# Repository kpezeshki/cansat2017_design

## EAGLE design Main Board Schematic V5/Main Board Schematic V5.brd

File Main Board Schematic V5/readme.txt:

Readme File for Printed Circuit Board 'GWC Cansat 2017 V4'

Board Specification
Size           89 x 100mm
Material       FR4
No of Layers   3
Thickness      1.6
Finish         HASL (Lead free) (RoHS)
Copper Weight  1.0oz

Special Requirements
Please cut where dimension layer specifies 'CHIP CUTOUT' and the surrounding hashed area.
Please cut where dimension layer specifies 'BOARD CUT' and the hashed area below it. 
Where possible please insert a silkscreen logo using the included file 'tLogo.bmp' in the space provided and named '[LOGO]' on the top silkscreen layer.

The design does not contain Blind Vias		
The design does not contain Buried Vias		
The design does not contain holes smaller than 0.25mm (0.010inches) 

The design conforms to the following design rules

Minimum track thickness 6 mil (0.15mm)
Minimum track clearance 6 mil (0.15mm)  --Not sure, please email 'ccameron12@gwc.org.uk' if there is a problem.

Layer Description
(Note: Inner layers are counted from the top downwards)

Top Silk Screen Overlay		Main Board Schematic V5.GTO
Top Solder Mask			Main Board Schematic V5.GTS
Top Copper			Main Board Schematic V5.GTL
Middle copper			Main Board Schematic V5.LY2
Bottom Copper			Main Board Schematic V5.GBL
Bottom Solder Mask		Main Board Schematic V5.GBS
Bottom Silk Screen		Main Board Schematic V5.GBO
Drill File			Main Board Schematic V5.TXT
Mill Layer			Main Board Schematic V5.GML

Contact Information

Invoice Address
Name           Charles Cameron
Company        GWC Cansat
Address        18 Barnshot Road
City           Edinburgh
County         City of Edinburgh
PostCode       EH13 0DJ
Email          kpezeshki11@gwc.org.uk
Phone          07759796855

Delivery Address
Name           Charles Cameron
Company        GWC Cansat
Address        18 Barnshot Road
City           Edinburgh
County         City of Edinburgh
PostCode       EH13 0DJ
Email          kpezeshki11@gwc.org.uk
Phone          07759796855

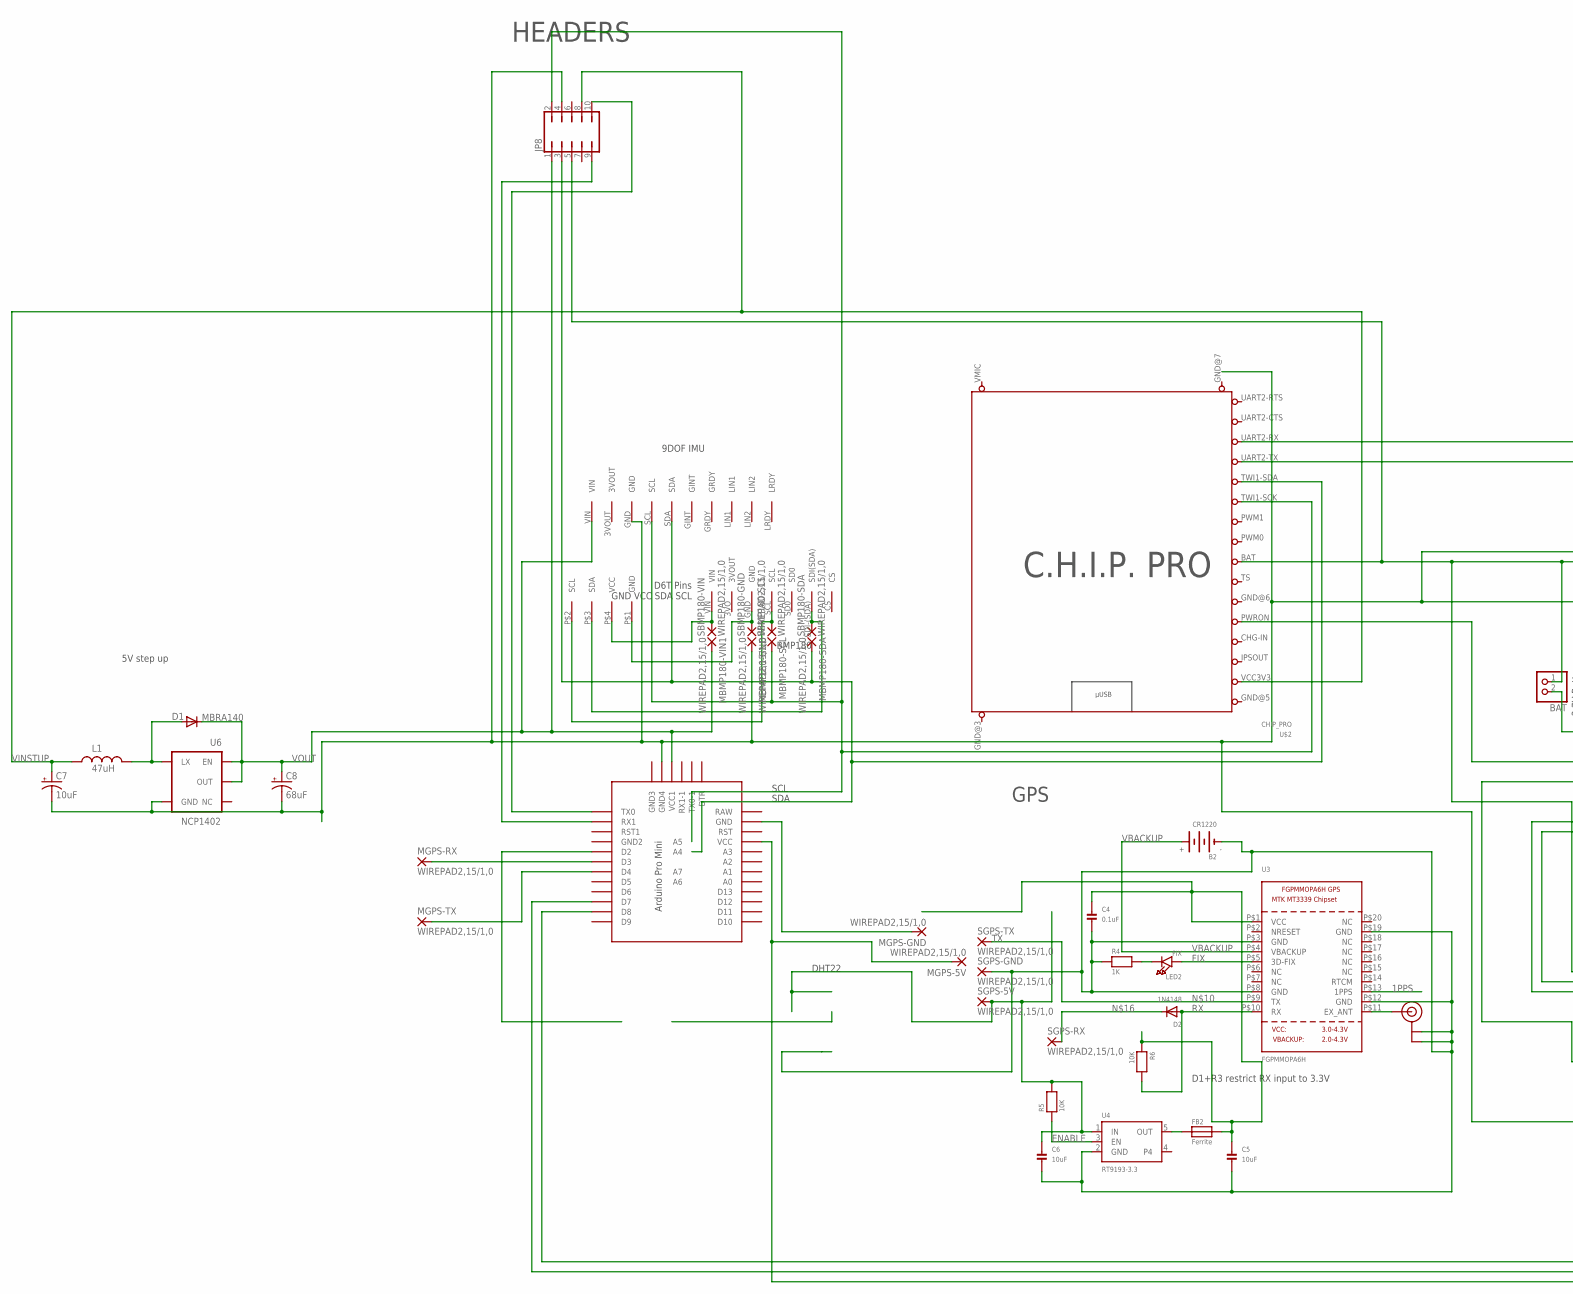
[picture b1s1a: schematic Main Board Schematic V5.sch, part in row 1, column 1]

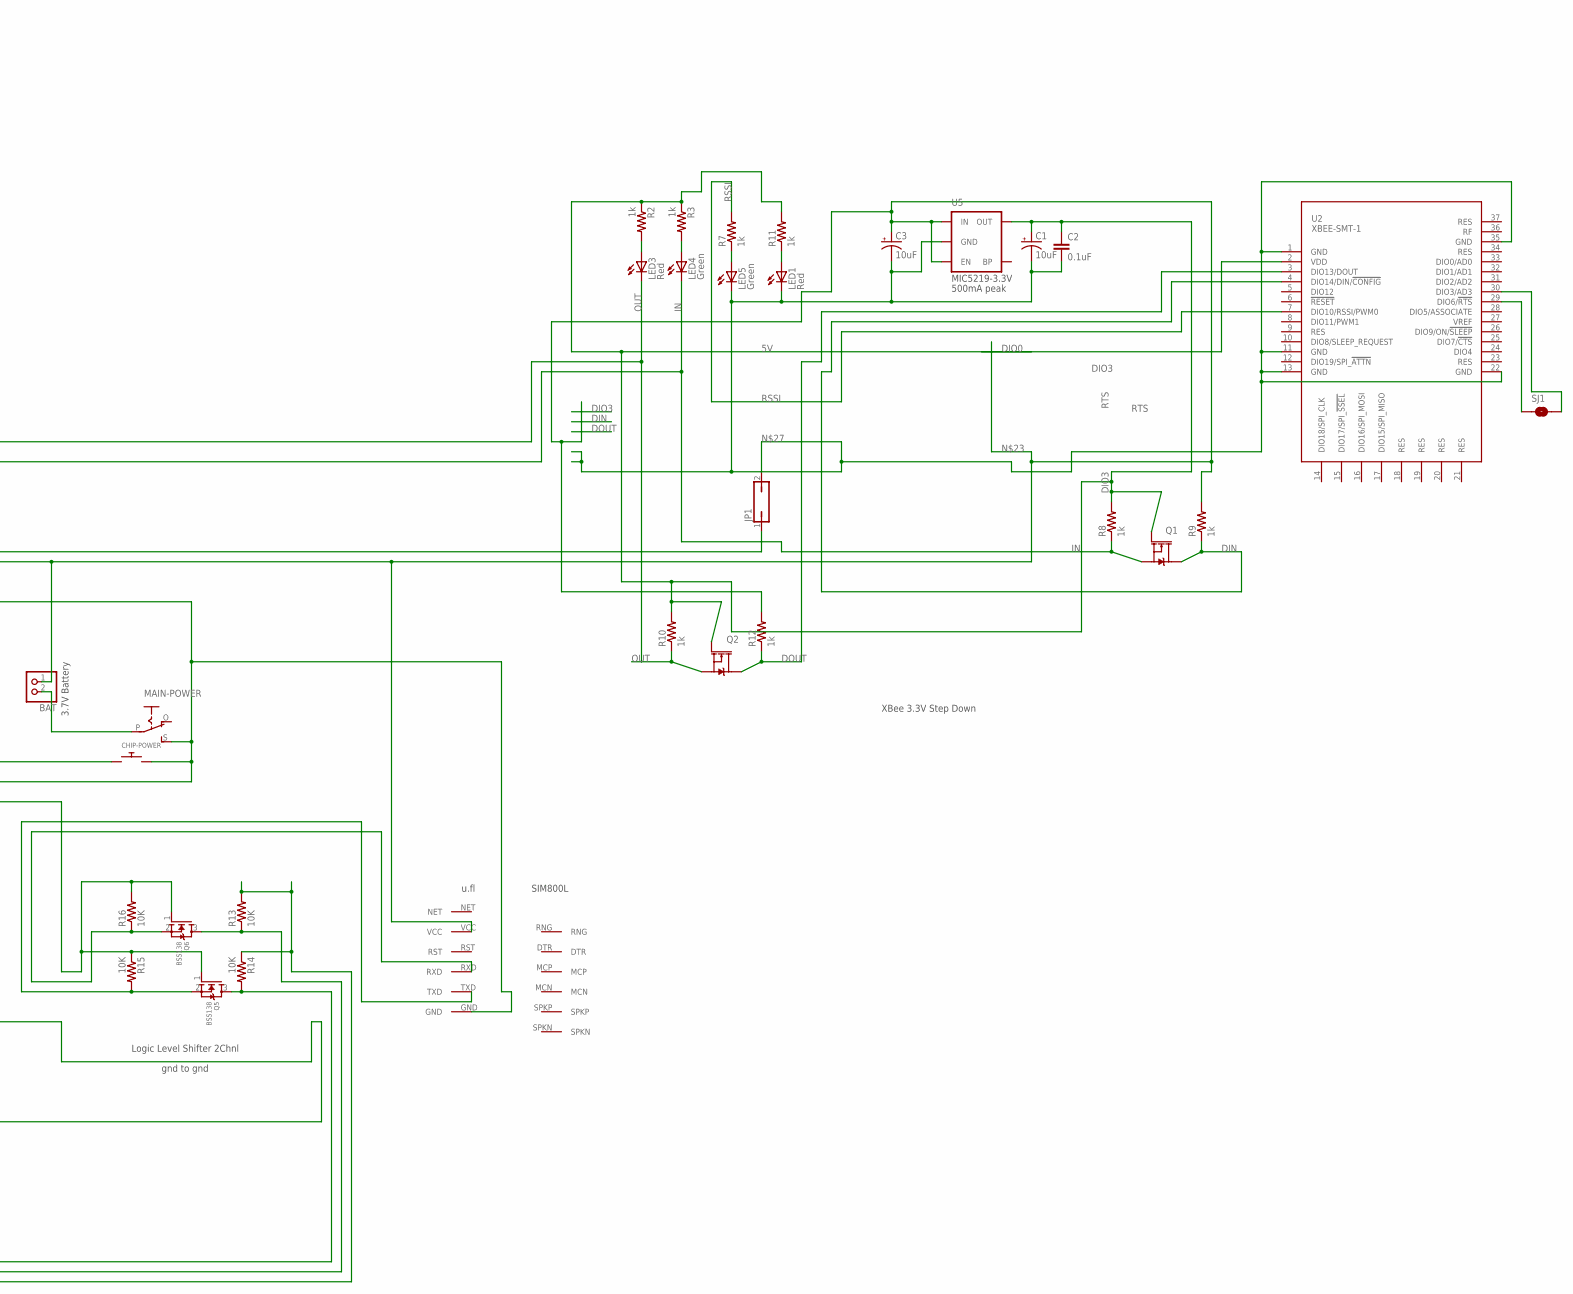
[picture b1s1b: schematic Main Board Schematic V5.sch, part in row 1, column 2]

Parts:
B2: CR1220
BAT: JST_2PIN-THM-RA; JST-PH-2-THM-RA
C1, C3, C7: 10uF; EIA3216
C2: 0.1uF; 0402-CAP
C4: 0.1uF; 0805
C5, C6: 10uF; 0805
C8: 68uF; EIA3528
CHIP-POWER: SWITCH_PUSHBUTTONEVQ-PE; TACT_PANA-EVQ
D1: MBRA140; SMA-DIODE
D2: 1N4148; SOD-323F
FB2: Ferrite; 0805
JP1: JP1Q; JP1
JP8: JP5Q
L1: 47uH; CR54
LED1, LED3: Red; LED-0603
LED2: FIX; CHIPLED_0805
LED4, LED5: Green; LED-0603
MAIN-POWER: EG1218S; EG1218
MBMP180-GND, MBMP180-SCL, MBMP180-SDA, MBMP180-VIN1: WIREPAD2,15/1,0; 2,15/1,0
MGPS-5V: WIREPAD2,15/1,0; 2,15/1,0
MGPS-GND: WIREPAD2,15/1,0; 2,15/1,0
MGPS-RX: WIREPAD2,15/1,0; 2,15/1,0
MGPS-TX: WIREPAD2,15/1,0; 2,15/1,0
Q1, Q2: 5.8A/30V/35mΩ; SOT23-3
Q5, Q6: BSS138; SOT23
R2, R3, R7, R8, R9, R10, R11, R12: 1k; 0402-RES
R4: 1K; 0805
R5, R6: 10K; 0805
R13, R14, R15, R16: 10K; R0805
SBMP180-GND, SBMP180-SCL, SBMP180-SDA, SBMP180-VIN: WIREPAD2,15/1,0; 2,15/1,0
SGPS-5V: WIREPAD2,15/1,0; 2,15/1,0
SGPS-GND: WIREPAD2,15/1,0; 2,15/1,0
SGPS-RX: WIREPAD2,15/1,0; 2,15/1,0
SGPS-TX: WIREPAD2,15/1,0; 2,15/1,0
SJ1: SOLDERJUMPERNO; SJ_2S-NO
U2: XBEE-SMT-1; XBEE-SMT
U3: FGPMMOPA6H
U4: RT9193-3.3; SOT23-5
U5: V_REG_LDOSMD; SOT23-5@1
U6: NCP1402; SOT23-5
U$1: D6T
U$2: CHIP_PRO
U$3: BMP180PINOUTBMP180; BMP180
U$4: 9DOF
U$5: PRO-MINI-2
U$8: SIM800L
U$32: U.FL

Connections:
1PPS: U3.P$13 (1PPS)
5V: C1.A (+), C2.1, Q1.1 (G), Q2.1 (G), R2.1, R3.1, R8.2, R10.2, R11.2, U2.2 (VDD), U5.5 (OUT)
A1: Q6.2 (S), R16.1, U$8.RXD
A2: Q5.2 (S), R15.2, U$8.TXD
B1: Q6.3 (D), R13.1, U$5.D7
B2: Q5.3 (D), R14.2, U$5.D8
CHG-IN: U$2.CHG-IN
DIN: Q1.3 (D), R9.1, U2.4 (DIO14/DIN/!CONFIG)
DIO3: SJ1.2, U2.30 (DIO3/AD3)
DOUT: Q2.3 (D), R12.1, U2.3 (DIO13/DOUT)
ENABLE: R5.1, U4.3 (EN)
FIX: LED2.A, U3.P$5 (3D-FIX)
GND: SBMP180-GND.1, U$1.P$1 (GND), U$2.GND@3 (GND), U$2.GND@5 (GND), U$2.GND@6 (GND), U$2.GND@7 (GND), U$3.GND
IN: LED4.C, Q1.2 (S), R8.1, U$2.UART2-TX
IPSOUT: U$2.IPSOUT
unnamed: LED2.C, R4.2
unnamed: BAT.2 (1), MAIN-POWER.P
unnamed: JP8.2, MBMP180-SCL.1, U$2.TWI1-SCK, U$4.SCL, U$5.A5
unnamed: FB2.1, U4.5 (OUT)
unnamed: U3.P$11 (EX_ANT), U$32.P$3 (SIGNAL)
unnamed: CHIP-POWER.P$1, U$2.PWRON
unnamed: JP8.3, MBMP180-SDA.1, U$2.TWI1-SDA, U$4.SDA, U$5.A4
unnamed: LED3.A, R2.2
unnamed: SGPS-TX.1, U3.P$9 (TX)
unnamed: LED4.A, R3.2
unnamed: JP8.10, U$5.TX0
unnamed: LED5.A, R7.1
unnamed: D1.A, L1.P$2 (2), U6.5 (LX)
unnamed: JP8.9, U$5.RX1
unnamed: D2.C, SGPS-RX.1
unnamed: MGPS-GND.1, U$5.GND
unnamed: SBMP180-VIN.1, U$1.P$4 (VCC), U$3.VIN
unnamed: SBMP180-SCL.1, U$1.P$2 (SCL), U$3.SCL
unnamed: SBMP180-SDA.1, U$1.P$3 (SDA), U$3.SDI-(SDA) (SDI(SDA))
unnamed: BAT.1 (2), C3.+, JP8.5, Q5.1 (G), Q6.1 (G), R9.2, R12.2, R15.1, R16.2, U5.1 (IN), U5.3 (EN), U$2.BAT, U$8.VCC
unnamed: C4.1, C5.1, FB2.2, R6.1, U3.P$1 (VCC)
unnamed: C1.C (-), C2.2, C3.-, JP1.2, LED1.C, LED5.C, U2.1 (GND), U2.11 (GND), U2.13 (GND), U2.22 (GND), U2.35 (GND), U5.2 (GND)
unnamed: MGPS-5V.1, R13.2, R14.1, U$5.VCC
unnamed: C6.1, R5.2, SGPS-5V.1, U4.1 (IN)
unnamed: B2.-, C4.2, C5.2, C6.2, R4.1, SGPS-GND.1, U3.P$3 (GND), U3.P$8 (GND), U3.P$12 (GND), U3.P$19 (GND), U4.2 (GND), U$32.P$1 (GND), U$32.P$2 (GND)
unnamed: C7.C (-), C8.C (-), CHIP-POWER.P$2, JP1.1, JP8.4, MAIN-POWER.S, MBMP180-GND.1, U6.4 (GND), U$4.GND, U$5.GND3 (GND4), U$8.GND
unnamed: LED1.A, R11.1
OUT: LED3.C, Q2.2 (S), R10.1, U$2.UART2-RX
RSSI: R7.2, U2.7 (DIO10/RSSI/PWM0)
RTS: SJ1.1, U2.29 (DIO6/!RTS)
RX: D2.A, R6.2, U3.P$10 (RX)
RX_5V: MGPS-RX.1, U$5.D3
TX: MGPS-TX.1, U$5.D4
VBACKUP: B2.+$1 (+), U3.P$4 (VBACKUP)
VINSTUP: C7.A (+), JP8.8, L1.P$1 (1), U$2.VCC3V3
VOUT: C8.A (+), D1.C, JP8.1, MBMP180-VIN1.1, U6.1 (EN), U6.2 (OUT), U$4.VIN, U$5.VCC1

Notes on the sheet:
D1+R3 restrict RX input to 3.3V
GPS
DHT22
BMP180
9DOF IMU
D6T Pins GND VCC SDA SCL
3.7V Battery
Logic Level Shifter 2Chnl
SIM800L
HEADERS
SCL
SDA
MIC5219-3.3V
500mA peak
5V step up
XBee 3.3V Step Down
gnd to gnd

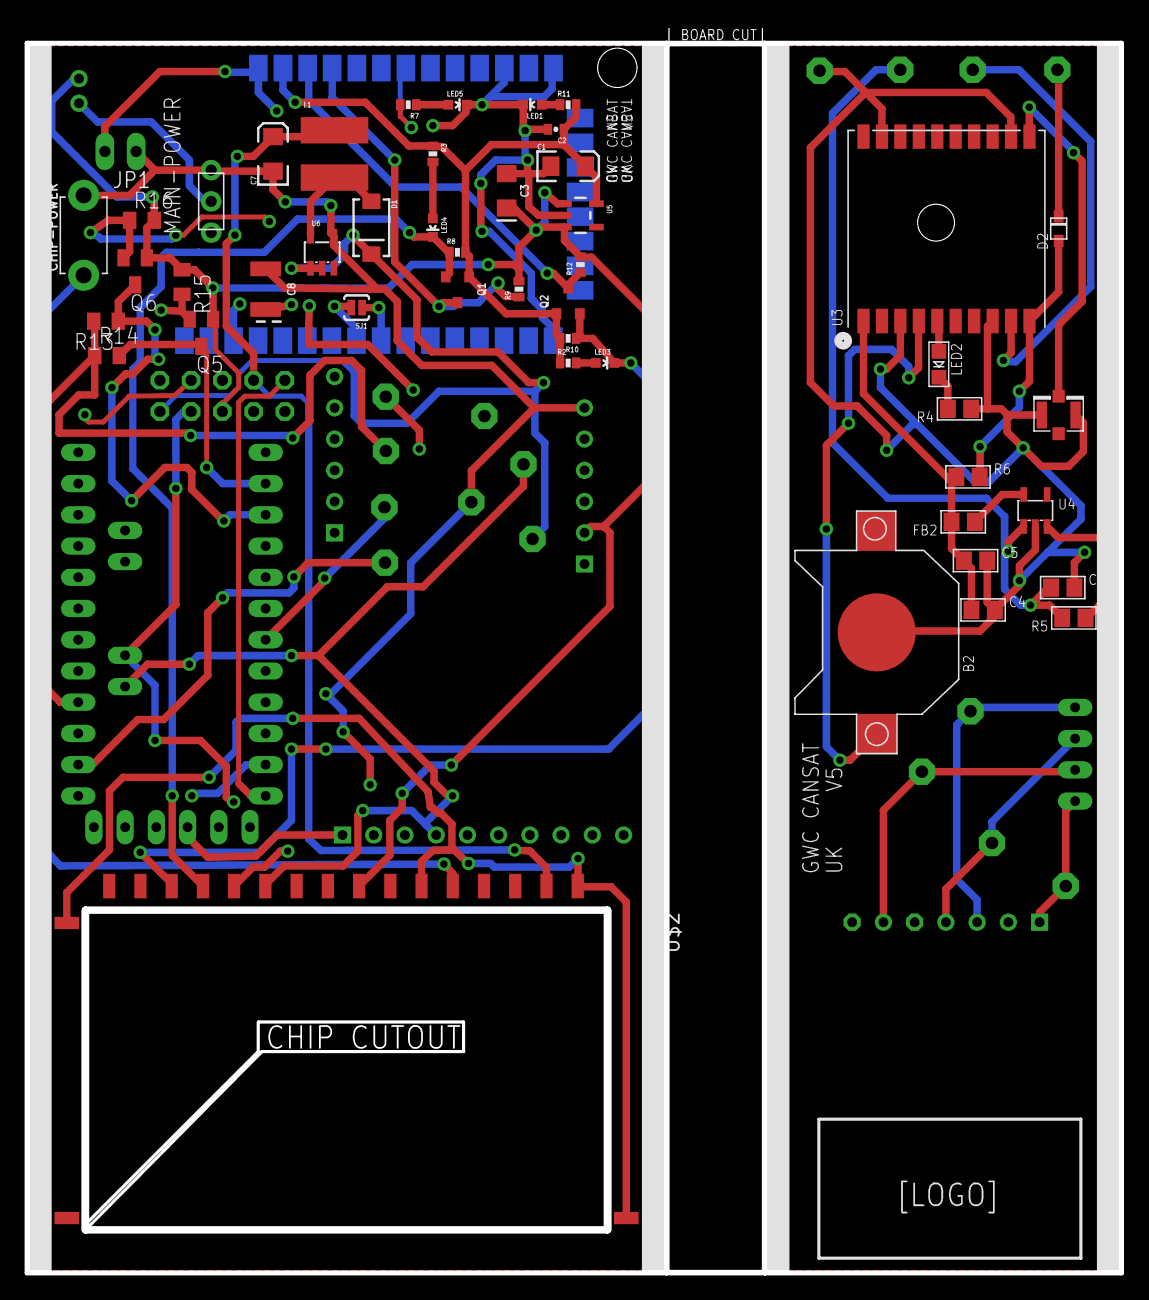
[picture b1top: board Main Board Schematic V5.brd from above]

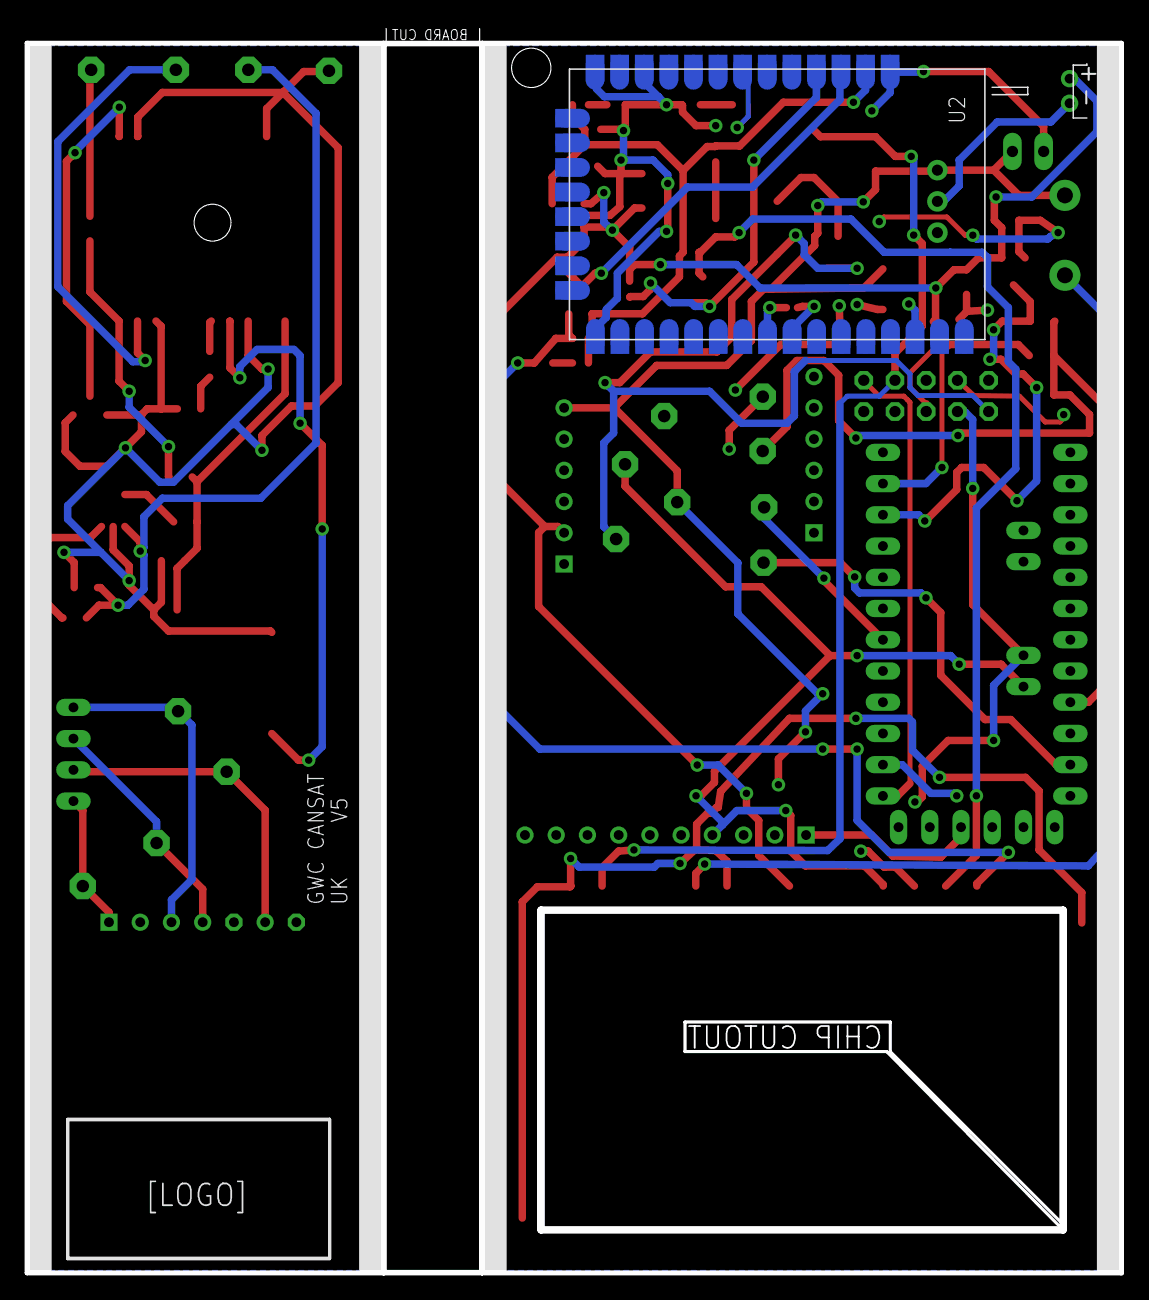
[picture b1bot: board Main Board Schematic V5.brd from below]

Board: 2 copper layers, 88.8 x 101.1 mm, 71 parts (2 on the bottom side), 48 nets.

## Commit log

2017-06-15 added design files
2017-06-26 added README

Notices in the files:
parts and their libraries:
SparkFun-DiscreteSemi: Licensing: CC v3.0 Share-Alike You are welcome to use this library for commercial purposes.
SparkFun-Capacitors: Licensing: Creative Commons ShareAlike 4.0 International - https://creativecommons.org/licenses/by-sa/4.0
